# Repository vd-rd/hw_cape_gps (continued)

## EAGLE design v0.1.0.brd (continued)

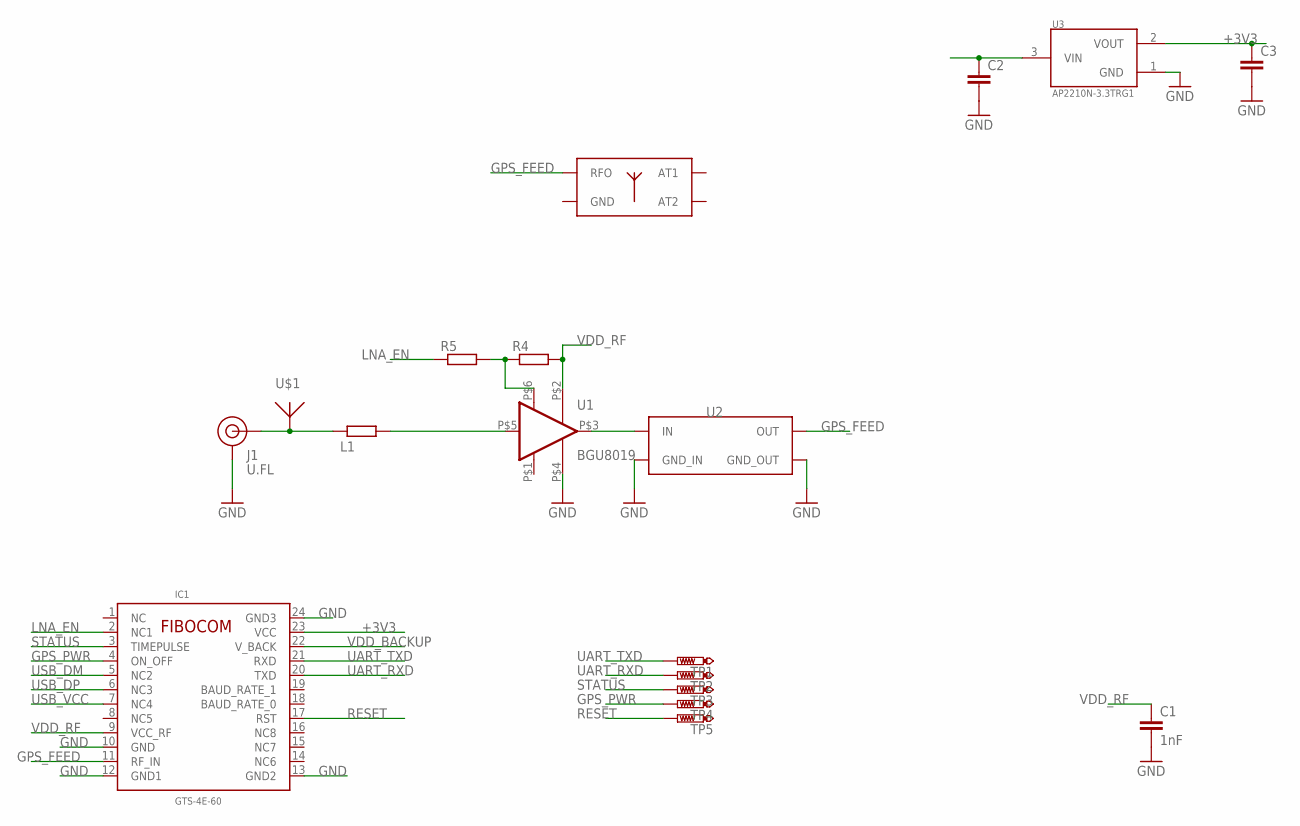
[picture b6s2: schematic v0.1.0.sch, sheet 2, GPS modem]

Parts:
ANT1: M20047; PCBCOMPONENT_1
C1: 1nF; C0402
C2, C3: C-EUC0805; C0805
IC1: GTS-4E-60; _GTS_4E_60
J1: U.FL
L1: R-EU_R0402; R0402
R4, R5: R-EU_R0402; R0402
TP1, TP2, TP3, TP4, TP5: PTR1B1,27; B1,27
U1: BGU8019; XSON6
U2: B3916B8813P810; XSON5
U3: AP2210N-3.3TRG1; SOT95P280X145-3N
U$1: ANT1590-2540A; 2540A

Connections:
+3V3: C3.1, IC1.23 (VCC), U3.2 (VOUT); also elsewhere on the board
GND: ANT1.2 (GND), ANT1.3 (GND), ANT1.4 (GND), C1.2, C2.2, C3.2, IC1.10 (GND), IC1.12 (GND1), IC1.13 (GND2), IC1.24 (GND3), J1.1 (GND), J1.2 (GND), U1.P$1 (GND), U1.P$4 (GND_RF), U2.2 (GND_IN), U2.3 (GND_OUT), U2.5 (GND_IN), U3.1 (GND); also elsewhere on the board
GPS_FEED: ANT1.5 (RFO), IC1.11 (RF_IN), U2.4 (OUT)
GPS_PWR: IC1.4 (ON_OFF), TP4.TP
LNA_EN: IC1.2 (NC1), R5.1
unnamed: J1.FEED (SIGNAL), L1.1, U$1.P$1
unnamed: U1.P$3 (RF_OUT), U2.1 (IN)
unnamed: R4.1, R5.2, U1.P$6 (ENABLE)
unnamed: L1.2, U1.P$5 (RF_IN)
unnamed: C2.1, U3.3 (VIN)
RESET: IC1.17 (RST), TP5.TP; also elsewhere on the board
STATUS: IC1.3 (TIMEPULSE), TP3.TP; also elsewhere on the board
UART_RXD: IC1.20 (TXD), TP2.TP
UART_TXD: IC1.21 (RXD), TP1.TP
USB_DM: IC1.5 (NC2); also elsewhere on the board
USB_DP: IC1.6 (NC3); also elsewhere on the board
USB_VCC: IC1.7 (NC4); also elsewhere on the board
VDD_BACKUP: IC1.22 (V_BACK)
VDD_RF: C1.1, IC1.9 (VCC_RF), R4.2, U1.P$2 (VCC)

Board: 2 copper layers, 26 parts (2 on the bottom side), 23 nets, no tracks yet.

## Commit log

2018-12-10 Add README.md
2018-12-10 Upload New File
2018-12-11 added gitignore
2018-12-13 new board version
2018-12-14 added eeprom, level shifter and routed traces
2018-12-14 drc fixes
2018-12-14 added values for parts
2018-12-21 new revision, dropped usb, added load switch
2018-12-30 relayout
2019-01-01 pre release fixes
2019-01-06 modified design according to bench findings
2019-01-07 add info about module
2019-01-07 Add new file
2019-01-07 added assets and cleaned up
2019-01-07 cosmetic fixes
2019-01-07 fixed values for components
2019-01-07 added mfgr aiding
2019-01-07 added usb connector
2019-01-17 added documentation
2019-01-20 updated docs
2019-01-20 Add board render
2019-01-22 added antennas
2019-01-23 added output files
2019-03-12 space optimisation
2019-05-02 project: update structure
2019-05-20 board: remove unused features
2019-05-21 project: release v1.1.0 is finished
2019-05-22 board: fixed connector error
2019-05-22 board: fixed legend for connector
